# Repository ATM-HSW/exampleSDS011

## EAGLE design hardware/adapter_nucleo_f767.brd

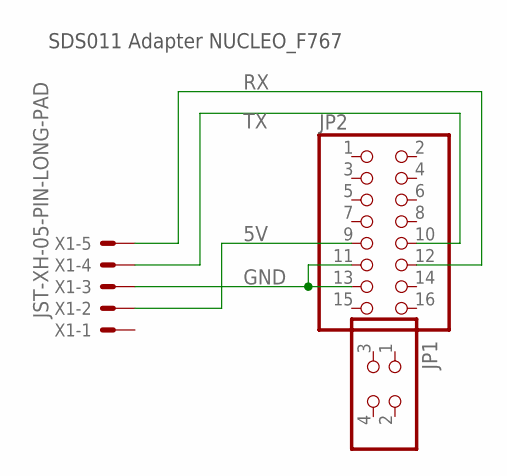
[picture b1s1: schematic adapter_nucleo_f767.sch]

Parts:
JP1: PINHD-2X2; 2X02
JP2: PINHD-2X8; 2X08
X1: JST-XH-05-PIN-LONG-PAD; JST-XH-05-PACKAGE-LONG-PAD

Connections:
5V: JP2.9, X1.2
GND: JP2.11, JP2.13, X1.3
RX: JP2.12, X1.5
TX: JP2.10, X1.4

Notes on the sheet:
SDS011 Adapter NUCLEO_F767

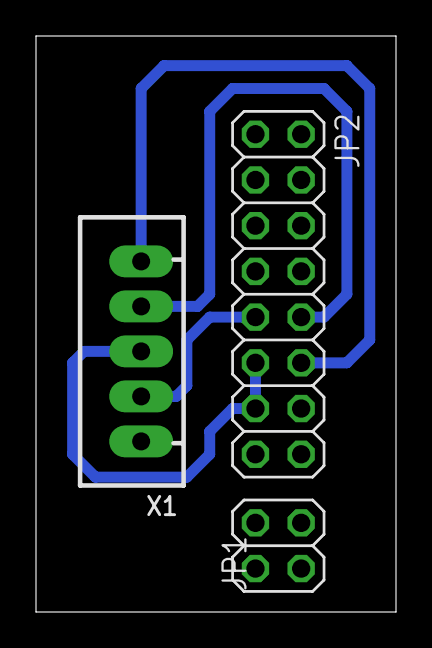
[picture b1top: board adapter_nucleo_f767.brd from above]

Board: 2 copper layers, 20.0 x 32.0 mm, 3 parts (0 on the bottom side), 4 nets.

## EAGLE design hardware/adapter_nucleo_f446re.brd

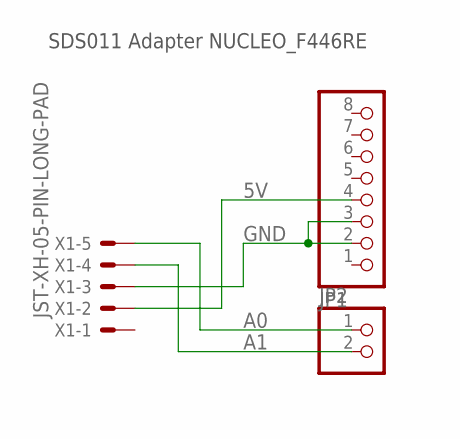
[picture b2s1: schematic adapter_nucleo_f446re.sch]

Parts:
JP1: PINHD-1X8; 1X08
JP2: PINHD-1X2; 1X02
X1: JST-XH-05-PIN-LONG-PAD; JST-XH-05-PACKAGE-LONG-PAD

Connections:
5V: JP1.4, X1.2
A0: JP2.1, X1.5
A1: JP2.2, X1.4
GND: JP1.2, JP1.3, X1.3

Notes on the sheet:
SDS011 Adapter NUCLEO_F446RE

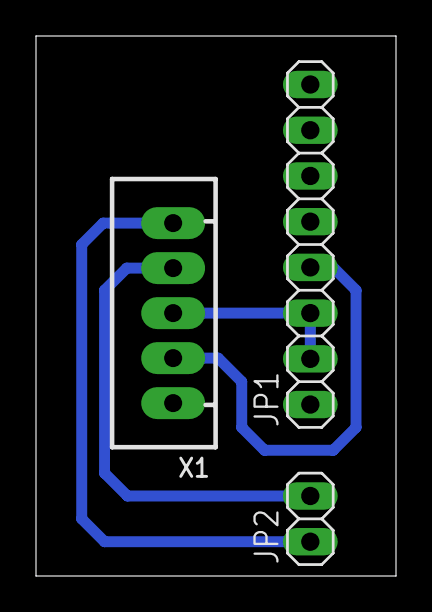
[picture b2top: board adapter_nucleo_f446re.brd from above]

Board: 2 copper layers, 20.0 x 30.0 mm, 3 parts (0 on the bottom side), 4 nets.
